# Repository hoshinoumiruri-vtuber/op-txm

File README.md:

# op-txm — Transformer-Output Condenser Microphone

Solid-state condenser microphone with transformer-balanced output.

---

## Table of Contents

1. [System Architecture](#1-system-architecture)
2. [Technical Specifications](#2-technical-specifications)
3. [Output Transformer — Neutrik NTE10/3](#3-output-transformer--neutrik-nte103)
4. [Engineering Verification and Simulation Results](#4-engineering-verification-and-simulation-results)
5. [Toolchain](#5-toolchain)
6. [Getting Started](#6-getting-started)
7. [Project Phases](#7-project-phases)
8. [Repository Structure](#8-repository-structure)

---

## 1. System Architecture

```
[XLR Phantom 48V] --> [LR8 Pre-reg 35.2V + Charge Pump] --> [JFET Input Buffer + DC Servo]
                              |                                            |
                        [TPS7A3901 +/-15V]                   [K47/K87 De-emphasis EQ]
                                                                           |
                                                          [NTE10/3 Output Transformer 1:3]
                                                                           |
                                                                    [XLR Balanced Out]
```

| Stage | Description |
|---|---|
| Power | LR8 pre-regulator (48V phantom → 35.2V). Diode charge pump → V_BOOST for JFET drain. TPS7A3901 WSON-12 → ±15V op-amp supply. Total draw 9.1 mA typ (< 10 mA IEC 61938). |
| Input | High-Z JFET buffer (MMBF170LT1G SOT-23) with op-amp DC servo for bias stability. |
| EQ | Active de-emphasis network tuned for K67/K87. Flat (K47) or −6 dB shelf above ~22 kHz (K87) via SJ1 solder bridge. |
| Output | Neutrik NTE10/3, reversed 3:1 connection (op-amp drives 3× winding, XLR from 1× winding): transformer-balanced, galvanic isolation, passive CMRR, Zout ≈ 255 Ω. |

---

## 2. Technical Specifications

| Parameter | Value |
|---|---|
| Supply | +48V phantom power (IEC 61938) |
| Internal rail | 35.2V (LR8 pre-reg) → ±15V (TPS7A3901); V_BOOST charge pump for JFET drain |
| Max current draw | < 10 mA (IEC 61938 phantom limit); typical 9.1 mA |
| Capsule | Takstar K87, 34 mm rim-terminated |
| Capsule compatibility | K47 (flat) and K87/K67 (de-emphasised) via SJ1 solder bridge |
| PCB form factor | 40×100 mm |
| Mounting | 4× M2.2 NPTH, rectangular pattern (30×80 mm) |
| Assembly | SMD for all active/passive components; through-hole for capsule leads and NTE10/3 transformer leads |
| De-emphasis network | R_shelf = 47 kΩ, C_deemph = 150 pF — −6 dB shelf above ~22 kHz |
| Output stage | Neutrik NTE10/3, reversed 3:1 connection (−9.5 dB, Zout ≈ 255 Ω) — standard Neumann/AKG practice |
| EQ op-amp | OPA1642AIDR (dual JFET-input, GBW=11 MHz, EIN=5.1 nV/√Hz) |
| Output balance | Transformer CMRR (passive) — no active output op-amp required |
| Output impedance | ~540 Ω referred to secondary (JFET 60Ω × n²=9) |

---

## 3. Output Transformer — Neutrik NTE10/3

### Confirmed specifications

| Parameter | Value | Source |
|---|---|---|
| Turns ratio | 1:3:10 (two secondary taps) | Neutrik datasheet |
| Selected tap | 1:3 (secondary = 1.8 kΩ) | Design choice |
| Primary impedance | 200 Ω | Neutrik / Farnell |
| Secondary impedance (1:3 tap) | 1.8 kΩ | Neutrik / Farnell |
| Secondary impedance (1:10 tap) | 20 kΩ | Neutrik / Farnell |
| Frequency response | 40 Hz – 20 kHz ±0.5 dB | Distributor spec |
| Solderability | IEC 68-2-20 compliant | Neutrik datasheet |
| Primary inductance | ~80 H (community measurement) | GroupDIY forum |
| Primary DCR (1× winding) | 105 Ω ±5% | Neutrik datasheet |
| Secondary DCR (3× winding) | 1.25 kΩ ±5% | Neutrik datasheet |
| Leakage inductance | **TBD — measure at bench** | — |

> After bench measurement, update DCR and leakage inductance values in `sim/tx_output.py` and `sim/signal_chain.py`.

### Wiring / connection — reversed 3:1 (Neumann/AKG standard)

Op-amp EQ output drives the **3× (secondary) winding**; XLR balanced output comes from the **1× (primary) winding**.

```
NTE10/3 lead colour (typical) — reversed 3:1 connection:
  3× winding (driven by EQ op-amp):
    Blue  → EQ op-amp output (hot drive)
    White → Signal GND (3× winding return)
    Yellow→ Centre tap → signal GND (if used; tie to GND or leave floating)
  1× winding (XLR balanced output):
    Red   → XLR pin 2 (hot)
    Black → XLR pin 3 (cold)
```

> **Verify lead colours against the physical unit** — Neutrik wire colours are not always consistent across production batches. Use an LCR meter to confirm winding connections before soldering.

### PCB mounting

The NTE10/3 is an encapsulated off-board transformer connected via its free wires. It is **not** mounted on the PCB directly.

- Solder the five leads to through-hole pads on the PCB (1.0 mm drill, 2.5 mm annular ring recommended)
- Secure the transformer body inside the mic capsule body with two cable ties through 2.5 mm NPTH slots at the PCB edge (or adhesive mount to the capsule basket)
- Allow enough wire slack for the transformer to not stress the PCB pads

---

## 4. Engineering Verification and Simulation Results

All simulations run analytically (Python) with ngspice batch mode for transient verification.

### 4.1 Power Stage

72V boost stage (Cockcroft-Walton charge pump), LR8 pre-regulator, TPS7A39 ±15V.

| Parameter | Value | Status |
|---|---|---|
| 72V rail ripple (after LC filter) | 0.088 µV p-p | PASS |
| LR8 junction temperature | 63.0 °C (45 °C ambient) | PASS |
| TPS7A39 junction temperature | 48.7 °C (45 °C ambient) | PASS |
| Phantom current draw | 9.09 mA typ / 10.97 mA max | PASS typ (< 10 mA IEC 61938) |

### 4.2 JFET Buffer + DC Servo

MMBF170 JFET, OPA2134 servo, Vdrain locked to 36 V ±1 V across 0–50 °C.

| Parameter | Value | Status |
|---|---|---|
| gm at operating point | 16.18 mA/V | — |
| Gain drift over temperature | 0.0 dB | PASS |
| Servo phase margin | 90° | PASS |
| EIN @ 1 kHz | 13.01 nV/√Hz | — |

### 4.3 K47/K87 De-emphasis EQ

| Frequency | K47 gain | K87 gain |
|---|---|---|
| 20 Hz | 0.00 dB | 0.00 dB |
| 1 kHz | 0.00 dB | −0.03 dB |
| 10 kHz | 0.00 dB | −1.74 dB |
| 20 kHz | 0.00 dB | −3.65 dB |

Phase margin ≥ 90° across all EQ states.

### 4.4 Full Signal Chain (sim/signal_chain.py) — ngspice PASS

K47/K87 modes, JFET → OPA1642 EQ → NTE10/3 → 600 Ω balanced load.

| Parameter | Value | Notes |
|---|---|---|
| Differential gain @ 1 kHz (K47) | +16.0 dB | Balanced output, reversed 3:1 TX |
| Differential gain @ 20 kHz (K47) | +16.0 dB | Flat within 0.1 dB |
| K87 shelf @ 20 kHz | −3.7 dB | Expected — shelf corner is 22.6 kHz |
| K87 shelf @ 100 kHz | −5.9 dB | PASS (target −6 dB ±1.5 dB) |
| Bandwidth LF −3 dB (K47) | 10.2 Hz | Sub-Hz with servo-locked Q-point |
| Bandwidth HF −3 dB (K47) | > 100 kHz | Well above audio band |
| Phase @ 1 kHz (K47) | +0.5° | — |
| Transformer connection | Reversed 3:1 (−9.5 dB) | Op-amp drives 3× winding; Zout ≈ 255 Ω at XLR |
| Transformer LF −3 dB | ~0.30 Hz | Estimated (Ldriven=720 H, DCR_sec=1.25 kΩ) |
| Transformer HF −3 dB | ~415 kHz analytical | Estimated (Lleak TBD at bench); reversed 3:1 extends HF vs forward |

> Transformer DCR and leakage inductance are estimated. Update `sim/tx_output.py` and `sim/signal_chain.py` after bench measurement.

---

## 5. Toolchain

| Tool | Purpose | Version |
|---|---|---|
| Python | Primary language | 3.12+ |
| uv | Package and environment management | 0.11.8+ |
| ngspice | SPICE simulation engine | 46 |
| PySpice | Python wrapper for ngspice | 1.5 |
| KiCad | PCB design (code-driven layout via kiutils) | 10.0.3+ |
| numpy / scipy | Numerical analysis | 2.4 / 1.17 |
| matplotlib | Plotting | 3.10 |

> **PCB layout is code-driven** — kiutils scripts generate the KiCad PCB file. See `docs/pcb_routing_knowhow.md` for routing rules and constraints.

> **ngspice -b batch mode** — do not use PySpice's `NgSpiceShared` API (unreliable with ngspice 42+).

---

## 6. Getting Started

### Prerequisites

```bash
# Arch Linux
sudo pacman -S ngspice kicad

# Ubuntu / Debian
sudo apt install ngspice kicad
```

### Python Environment

```bash
uv sync
```

### Running Simulations

```bash
source .venv/bin/activate

# Power stage
python sim/boost_72v.py

# JFET buffer + DC servo
python sim/dc_servo.py

# K47/K87 de-emphasis EQ
python sim/dual_capsule_eq.py

# Transformer output stage (update DCR/Lleak values first)
python sim/tx_output.py

# Generate all plots
python sim/generate_plots.py
```

### Generating PCB Files

The KiCad project is fully code-driven. Two scripts must be run before opening KiCad:

```bash
# 1. Generate the KiCad project file (net classes, DRC rules, HV net assignments)
python pcb/project.py        # → pcb/op-txm.kicad_pro

# 2. Generate the board layout (outline, component placement, GND fill zone)
python pcb/layout.py         # → pcb/op-txm.kicad_pcb + pcb/op_txm_layout.png
```

Open the project in KiCad 10:

```bash
kicad pcb/op-txm.kicad_pro
```

> Always open via `.kicad_pro`, not `.kicad_pcb` directly — the project file carries the HV net class assignments and DRC rules. If you regenerate either file, re-open the project in KiCad (the board file is reloaded automatically).

After opening in KiCad:
1. **Fill All Zones** (`B` key) — floods the B.Cu GND plane
2. **Run DRC** — verify zero clearance violations, zero unrouted nets flagged as errors
3. **Route remaining nets** interactively (capsule signal, HV supply, EQ → transformer)
4. **Export Gerbers** — `File → Fabrication Outputs → Gerbers`, output to `gerbers/`

---

## 7. Project Phases

### Phase 1: Simulation — COMPLETE

- [x] Power stage simulation (boost_72v.py) — 0.088 µV ripple PASS
- [x] Phantom power budget (phantom_budget.py) — 9.09 mA typ PASS (< 10 mA IEC 61938)
- [x] JFET buffer + DC servo simulation (dc_servo.py)
- [x] K47/K87 EQ simulation (dual_capsule_eq.py)
- [x] Transformer output stage analytical model (tx_output.py) — LF=0.30 Hz, HF=415 kHz
- [x] Full signal-chain AC sweep (signal_chain.py) — 16.0 dB diff gain, K87 shelf −5.9 dB @ 100 kHz PASS
- [ ] Measure NTE10/3 DCR and leakage inductance (bench LCR meter) — deferred to Phase 4
- [ ] Update tx_output.py and signal_chain.py with measured values — deferred to Phase 4

### Phase 2: PCB Layout (code-driven via kiutils) — IN PROGRESS

- [x] Add kiutils to pyproject.toml, scaffold pcb/layout.py
- [x] Generate .kicad_pro (pcb/project.py) with HV net class and DRC rules
- [x] Define board outline: 35×85 mm, 4× M2.2 NPTH (30×80 mm pattern) — pcb/outline.py
- [x] Place components via script: power stage, JFET buffer, EQ, transformer TH pads
- [x] Define HV keepout zone (outline.py), B.Cu GND plane (layout.py)
- [x] Add NPTH zip-tie slots (2.5 mm) at PCB edge for transformer retention
- [x] Transformer bobbin cutout (10×8 mm interior rectangle, Edge.Cuts)
- [ ] Route critical nets (capsule signal, HV supply, EQ output) — interactive in KiCad
- [ ] DRC — zero clearance violations
- [ ] Fill All Zones, export Gerbers

### Phase 3: BOM + Procurement

- [x] Generate BOM (bom/generate_bom.py) — 31 line items, 35 SMD placements
- [x] DFM review (bom/txm_bom_dfm.txt) — board parameters, TH hand-solder notes
- [ ] Order NTE10/3 (check stock: Farnell, Mouser)
- [ ] Order long-lead parts: IXYS LR8, TPS7A3901

### Phase 4: Bench Validation (hardware)

- [ ] Power-on: verify 35.2V LR8 rail, ±15V, V_BOOST
- [ ] DC servo: check Vdrain = 36V ±1V across 0–50°C
- [ ] Noise floor A-weighted (target < 14 dB-A)
- [ ] Frequency response 20Hz–20kHz (±1 dB)
- [ ] Output CMRR via transformer (target > 60 dB at 1 kHz)
- [ ] Phantom current draw (target < 7 mA)
- [ ] Acoustic evaluation

---

## 8. Repository Structure

```
op-txm/
├── pyproject.toml
├── README.md
├── sim/
│   ├── boost_72v.py          # Power stage simulation
│   ├── dc_servo.py           # JFET DC servo simulation
│   ├── dual_capsule_eq.py    # K47/K87 EQ simulation
│   ├── tx_output.py          # NTE10/3 transformer output stage
│   ├── generate_plots.py     # Batch plot generator
│   └── models/               # Ngspice device models
├── bom/
│   └── generate_bom.py       # BOM generator
├── pcb/                      # KiCad project files (code-driven layout)
│   └── notes.md              # PCB constraints and layout notes
├── docs/
│   └── pcb_routing_knowhow.md # Routing rules and constraints
└── assets/
    └── sim_results/           # Generated plots
```

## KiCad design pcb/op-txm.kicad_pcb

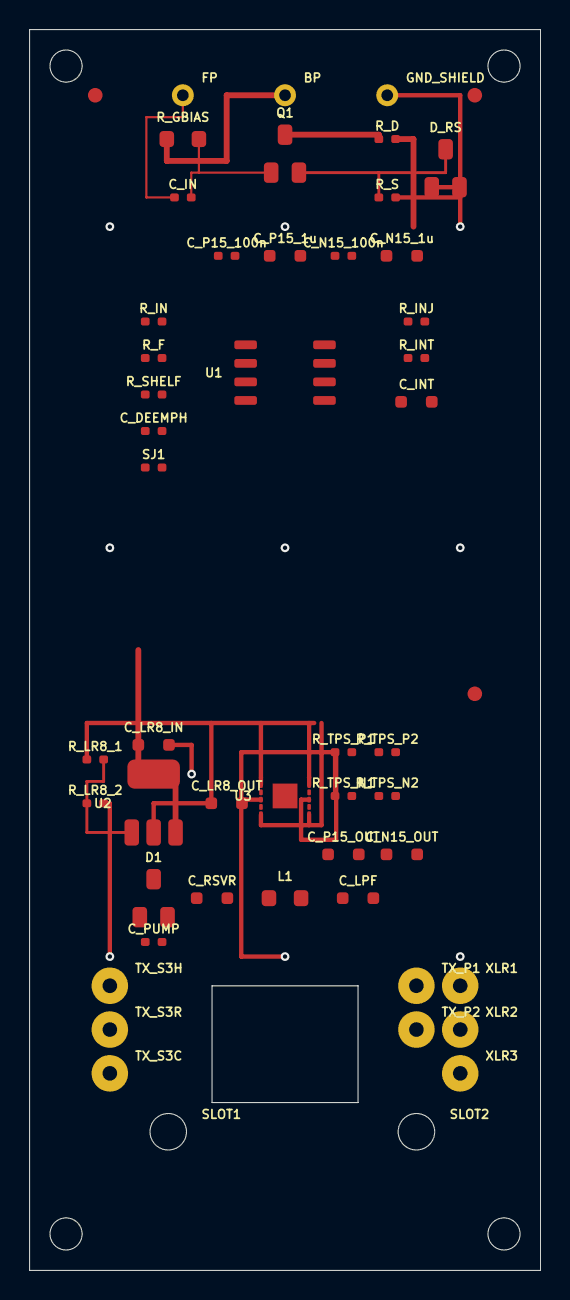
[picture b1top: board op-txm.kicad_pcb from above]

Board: 2 copper layers, 35.0 x 85.0 mm, 49 parts (0 on the bottom side), 19 nets.

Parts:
BP: CapsulePad
C_DEEMPH: 150p
C_IN: 10n
C_INT: 10u
C_LPF: 10u
C_LR8_IN: 10u/100V
C_LR8_OUT: 4u7
C_N15_1u: 1u
C_N15_100n: 100n
C_N15_OUT: 10u
C_P15_1u: 1u
C_P15_100n: 100n
C_P15_OUT: 10u
C_PUMP: 100n/100V
C_RSVR: 4u7/100V
D1: BAT54S
D_RS: HSMS-2820
FP: CapsulePad
GND_SHIELD: CapsulePad
L1: 10mH
Q1: MMBF170LT1G
R_D: 22k
R_F: 47k
R_GBIAS: 10M
R_IN: 10k
R_INJ: 1M
R_INT: 300k
R_LR8_1: 270k
R_LR8_2: 10k
R_S: 1k
R_SHELF: 47k
R_TPS_N1: 127k
R_TPS_N2: 10k
R_TPS_P1: 127k
R_TPS_P2: 10k
SJ1: SJ_K87
SLOT1, SLOT2: NPTH_Slot
TX_P1, TX_P2: THPad
TX_S3C, TX_S3H, TX_S3R: THPad
U1: OPA1642AIDR
U2: LR8
U3: TPS7A3901
XLR1, XLR2, XLR3: THPad

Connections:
BP_CAPSULE: BP.1, R_GBIAS.1
FP_CAPSULE: C_IN.1, FP.1
GND: C_LPF.2, C_LR8_IN.2, C_LR8_OUT.2, C_N15_1u.2, C_N15_100n.2, C_N15_OUT.2, C_P15_1u.2, C_P15_100n.2, C_P15_OUT.2, C_RSVR.2, D1.3, D_RS.1, D_RS.2, GND_SHIELD.1, R_LR8_2.2, R_S.2, R_TPS_N2.2, R_TPS_P2.2, TX_S3C.1, U1.3, U1.5, U3.EP, XLR1.1
LR8_ADJ: R_LR8_1.2, R_LR8_2.1, U2.1
N15V: C_N15_1u.1, C_N15_100n.1, C_N15_OUT.1, R_TPS_N1.1, U1.4, U3.4
P15V: C_P15_1u.1, C_P15_100n.1, C_P15_OUT.1, R_TPS_P1.1, U1.8, U3.9
P48V_LDO: C_LR8_OUT.1, R_LR8_1.1, U2.2, U3.1, U3.2, U3.6, U3.7, U3.11, U3.12
PHANTOM: C_LR8_IN.1, C_PUMP.1, D1.1, U2.3, U2.4
SIG_EQ: C_DEEMPH.1, C_DEEMPH.2, R_F.1, R_F.2, R_IN.2, R_SHELF.1, R_SHELF.2, SJ1.1, SJ1.2, U1.1, U1.2
SRV_INT: C_INT.1, R_INT.2, U1.6
SRV_OUT: C_INT.2, R_INJ.1, U1.7
TPS_FB_NEG: R_TPS_N1.2, R_TPS_N2.1, U3.3, U3.5
TPS_FB_POS: R_TPS_P1.2, R_TPS_P2.1, U3.8, U3.10
VDRAIN: Q1.3, R_D.1
VGATE: C_IN.2, Q1.1, R_GBIAS.2, R_INJ.2
VSOURCE: D_RS.3, Q1.2, R_IN.1, R_INT.1, R_S.1
V_BOOST: C_LPF.1, C_PUMP.2, C_RSVR.1, D1.2, L1.1, L1.2, R_D.2
XLR_COLD: TX_P2.1, XLR3.1
XLR_HOT: TX_P1.1, XLR2.1

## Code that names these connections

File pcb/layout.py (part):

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    "TPS_FB_NEG": 15,
    "TX_DRV_HOT": 16,    # 3× secondary hot (op-amp side)
    "TX_DRV_RTN": 17,    # 3× secondary return
    "XLR_HOT":    18,    # XLR pin 2 — from 1× primary
    "XLR_COLD":   19,    # XLR pin 3 — from 1× primary
    "BP_CAPSULE": 20,    # back-plate bias (V_BOOST via R_GBIAS)
    "FP_CAPSULE": 21,    # front-plate signal (→ VGATE)
}
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    #   Pin 5: IN+_B   Pin 6: IN-_B  Pin 7: OUT_B  Pin 8: V+
    # Section A = EQ (inverting), Section B = DC servo
    opa_nets = [
        "SIG_EQ",    # pin1: OUT_A (EQ output → transformer)
        "SIG_EQ",    # pin2: IN-_A (inverting; EQ feedback)
        "GND",       # pin3: IN+_A (non-inverting = AC GND via cap)
        "N15V",      # pin4: V-
        "GND",       # pin5: IN+_B (servo non-inverting = VREF)
        "SRV_INT",   # pin6: IN-_B (servo inverting = integrator node)
        "SRV_OUT",   # pin7: OUT_B (servo output → gate injection)
        "P15V",      # pin8: V+
    ]
    components.append(soic8("U1", "OPA1642AIDR", opa_nets, 100.0, 81.0))

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
    # U2: TPS7A4001 SOT-23-5 — 48V PHANTOM → 35.7V (U2_OUT) → D_PREREG → 35.4V (P48V_LDO)
    # Pad positions at (91, 110.5):
    #   pin1(IN/PHANTOM)=(89.85,111.45)  pin2(OUT/U2_OUT)=(89.85,110.5)
    #   pin3(ADJ)=(89.85,109.55)         pin4(EN/PHANTOM)=(92.15,110.025)
    #   pin5(GND)=(92.15,110.975)
    components.append(sot23_5("U2", "TPS7A4001",
                               "PHANTOM", "U2_OUT", "LR8_ADJ", "PHANTOM", "GND",
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
    # XLR cable pads — X=112 is ≥11 mm from bottom mounting hole at (115,140)
    components.append(th_pad("XLR1", "GND",      112.0, 123.0))  # pin 1 — shield
    components.append(th_pad("XLR2", "XLR_HOT",  112.0, 126.0))  # pin 2 — hot
    components.append(th_pad("XLR3", "XLR_COLD", 112.0, 129.0))  # pin 3 — cold

    # Cable-tie NPTH slots — Y=133 clears all TH pad rings and mounting holes
    # SLOT1(92,133): ≥5.66 mm from TX_S3C(88,129), ≥9.9 mm from MH(85,140)
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    # VGATE (high-Z, W_HIMP=0.15mm): R_GBIAS pad2 and C_IN pad2 → Q1 gate
    # Route at Y=66.0 (not 67.30) east of Q1 gate to avoid Q1 VSOURCE pad at (100.95,67.30)
    segments.extend([
        _seg(94.10,  65.00, 94.10,  66.00, "VGATE", W_HIMP),  # R_GBIAS pad2 down to Y=66
        _seg(94.10,  66.00, 99.05,  66.00, "VGATE", W_HIMP),  # east at Y=66
        _seg(99.05,  66.00, 99.05,  67.30, "VGATE", W_HIMP),  # down to Q1 gate
        _seg(93.575, 69.00, 93.575, 67.30, "VGATE", W_HIMP),  # C_IN pad2 up
        _seg(93.575, 67.30, 94.10,  67.30, "VGATE", W_HIMP),  # → join node
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    # Pad positions:
    #   C_LR8_IN(91,106.5) 0603: p1-PHANTOM=(89.95,106.5) p2-GND=(92.05,106.5)
    #   U2-TPS7A4001(91,110.5) SOT-23-5:
    #     pin1(IN/PHANTOM)=(89.85,111.45)  pin2(OUT/U2_OUT)=(89.85,110.5)
    #     pin3(ADJ/LR8_ADJ)=(89.85,109.55) pin4(EN/PHANTOM)=(92.15,110.025)
    #     pin5(GND)=(92.15,110.975)
    #   D_PREREG(92.5,110.5) SOD-123: anode(U2_OUT)=(91.25,110.5) cathode(P48V_LDO)=(93.75,110.5)
    #   R_LR8_1(87,107.5) 0402:  p1-U2_OUT=(86.425,107.5) p2-LR8_ADJ=(87.575,107.5)
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    # Local GND via for C_LR8_IN pad2
    vias.append(_gnd_via(93.6, 108.5))

    # PHANTOM: EN branch at Y=107.5; B.Cu via bypass routes pin1 from south
    # (left-column pads pin2/pin3 block north approach; B.Cu avoids the IC area)
    segments.extend([
        _seg(89.95, 106.5, 89.95, 100.0, "PHANTOM", W_HV),    # north stub -> Task I
        _seg(89.95, 106.5, 89.95, 107.5, "PHANTOM", W_HV),    # south to EN junction / via
        _seg(89.95, 107.5, 92.15, 107.5, "PHANTOM", W_HV),    # east to EN column
        _seg(92.15, 107.5, 92.15, 110.025, "PHANTOM", W_HV),  # south to pin4 (EN)
    ])
    vias.append(_net_via(89.95, 107.5, "PHANTOM"))                                   # F→B
    segments.append(_seg(89.95, 107.5, 89.95, 112.0, "PHANTOM", W_HV, "B.Cu"))      # B.Cu bypass
    vias.append(_net_via(89.95, 112.0, "PHANTOM"))                                   # B→F
    segments.extend([
        _seg(89.95, 112.0, 89.85, 112.0, "PHANTOM", W_HV),    # west jog to pin1 column
        _seg(89.85, 112.0, 89.85, 111.45, "PHANTOM", W_HV),   # north to pin1 (IN)
    ])

    # U2_OUT: pin2 east to D_PREREG anode; north to Y=108.5 (≥0.5mm from pin3 top Y=109.225)
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        _seg(94.95, 110.5,  94.95, 105.0, "P48V_LDO", W_POWER),  # up to trunk
    ])

    # LR8_ADJ (0.20 mm): R_LR8_1 p2 → T-junction at Y=109.55 → pin3 (ADJ) and R_LR8_2 p1
    segments.extend([
        _seg(87.575, 107.5,  87.575, 109.55, "LR8_ADJ"),           # R_LR8_1 p2 south
        _seg(87.575, 109.55, 89.85,  109.55, "LR8_ADJ"),           # east to pin3 (ADJ)
        _seg(87.575, 109.55, 86.425, 109.55, "LR8_ADJ"),           # west branch
        _seg(86.425, 109.55, 86.425, 110.5,  "LR8_ADJ"),           # south to R_LR8_2 p1
    ])
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        # R_LR8_2 pad2 → GND trunk at X=88
        _seg(87.575, 110.5, 88.0,  110.5, "GND", W_POWER),
        _seg( 88.0,  110.5, 88.0,  121.0, "GND", W_POWER),
        # U2 pin5 (GND) → south then east to X=97 trunk (avoids PHANTOM south trunk at X=89.95)
        _seg(92.15, 110.975, 92.15, 114.5, "GND", W_POWER),
        _seg(92.15,  114.5,  97.0,  114.5, "GND", W_POWER),
        # C_LR8_IN pad2 → local GND via at (93.6,108.5)
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        _seg( 97.0,  121.0, 100.0, 121.0, "GND", W_POWER),
    ])

    # ── Task G1: TPS7A3901 — P48V_LDO to IN pins ─────────────────────────
    # Left IN: p1(98.35,108.75), p2(98.35,109.25), p6(98.35,111.25)
    # Right IN: p12(101.65,108.75), p11(101.65,109.25), p7(101.65,111.25)
    # p6 and p7 approach from below: p3-p5 and p8-p10 (non-P48V_LDO) are in between
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        vias.append(_gnd_via(vx, vy))

    # ── Task C: DC servo (U1 section B) ──────────────────────────────────
    # U1 right pads X=102.7: pin7=SRV_OUT(80.365) pin6=SRV_INT(81.635)
    # R_INJ(109,77.5) 0402: p1=SRV_OUT(108.425,77.5) p2=VGATE(109.575,77.5)
    # R_INT(109,80.0) 0402: p1=VSOURCE(108.425,80.0) p2=SRV_INT(109.575,80.0)
    # C_INT(109,83.0) 0603: p1=SRV_INT(107.95,83.0) p2=SRV_OUT(110.05,83.0)
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    ])

    # ── Task D: U1 power pins ────────────────────────────────────────────
    # pin8=P15V (102.7,79.095): extend P15V trunk (X=103.5) north then west
    # pin4=N15V (97.3,82.905):  extend N15V trunk (X=97.0) north then east
    segments.extend([
        _seg(103.5, 107.0, 103.5,  79.095, "P15V", W_POWER),
        _seg(103.5,  79.095, 102.7, 79.095, "P15V", W_POWER),
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
    # ── Task B: Audio zone EQ (U1 section A) ─────────────────────────────
    # U1 SOIC-8 at (100,81), PITCH=1.27, left pads X=97.3, right pads X=102.7
    # pin1=OUT_A/SIG_EQ  (97.3, 79.095)
    # pin2=IN-_A/SIG_EQ  (97.3, 80.365)
    # EQ components at X=91: R_IN(77.5) R_F(80) R_SHELF(82.5) C_DEEMPH(85) SJ1(87.5)
    # SIG_EQ trunk at X=93.5, Y=[77.5..87.5]; VSOURCE from Q1 src to R_IN p1
    segments.extend([
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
